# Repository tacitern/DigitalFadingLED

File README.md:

# DigitalFadingLED
Microcontroller project which uses a usb virtual serial port to control the color of a RGB led, brightness and fade rate.

## Serial Commands

The FadingLED device waits for specific serial commands. The following table lists the specifc commands:

|Serial Command|Command Message|
| :---- | :---- |
| [Get Colors](#get-colors) | `"COLOR?\r\n"` |
| [Set Colors](#set-colors) | `"COLOR <Red>,<Green>,<Blue>\r\n"` |
| [Get Luminance](#get-luminance) | `"LUM?\r\n"` |
| [Set Luminance](#set-luminance) | `"LUM <Luminance>\r\n"` |
| [Get Rate](#get-rate) | `"RATE?\r\n"` |
| [Set Rate](#set-rate) | `"RATE <Rate>\r\n"` |
| [Get Save Data](#get-save-data) | `"SAVE?\r\n"` |
| [Set Save Date](#set-save-data) | `"SAVE\r\n"` |
| [Get ID](#get-id) | `"ID?\r\n"` |
| [Set ID](#set-id) | `"ID <ID number>\r\n"` |

### **Get Colors**

Returns current color settings as unsigned integer values from 0 to 255

*Serial Command:* `"COLOR?\r\n"`

*Return String:* `"Red <0 to 255>; Green <0 to 255>; Blue <0 to 255>;\n\r"`

---

### **Set Colors**

Sets the current color setting using provided unsigned interger values for 0 to 255

*Serial Command:* `"COLOR <Red>,<Green>,<Blue>\n\r"`

---

### **Get Luminance**

Returns the current brightness/luminance setting as an unsigned integer from 0 to 1000

*Serial Command:* `"LUM?\n\r"`

*Return String:* `<Luminance Value>\n\r`

---

### **Set Luminance**

Sets the current brightness/luminance setting using a provided unsigned interger from 0 to 1000, 0 to 100.0 percent.

*Serial Command:* `"LUM <Luminance>\r\n"`

---

### **Get Rate**

Returns the current rate setting as an unsigned integer from 0 to 255.

*Serial Command:* `"RATE?\n\r"`

*Return String:* `<Rate Value>\n\r`

---

### **Set Rate**

Sets the current brightness/luminance setting using a provided unsigned interger from 0 to 1000, 0 to 100.0 percent.

*Serial Command:* `"LUM <Luminance>\r\n"`

---

### **Get Save Data**

Returns the current settings saved in the on board EEPROM.

*Serial Command:* `"SAVE?\r\n"`

*Return String:* `"ID: <ID Setting>\nRED: <Red Value>\nGREEN: <Green Value>\nBLUE: <Blue Value>\nLUM: <Luminance Value>\nRATE: <Rate Value>\n\r"`

---

### **Set Save Data**

Saves the current settings in the on board EEPROM. The settings saved include:

* ID Value
* Red Value
* Green Value
* Blue Value
* Luminance Value
* Rate Value

*Serial Command:* `"SAVE\r\n"`

---

### **Get ID**

Returns the current ID number setting saved in the EEPROM.

*Serial Command:* `"ID?\n\r"`

*Return String:* `<ID Number>\n\r`

---

### **Set ID**

Sets the provided unsigned integer from 0 to 255 as an ID number to be saved in the EEPROM. 

*Serial Command:* `"ID <ID Number>\n\r"`

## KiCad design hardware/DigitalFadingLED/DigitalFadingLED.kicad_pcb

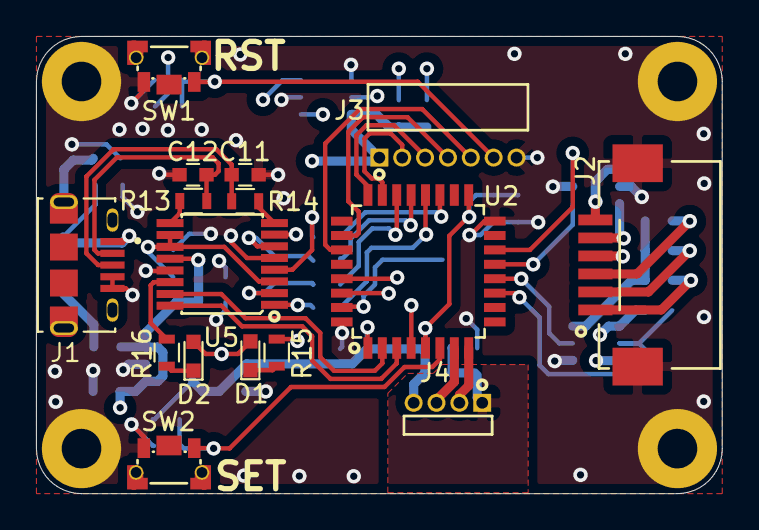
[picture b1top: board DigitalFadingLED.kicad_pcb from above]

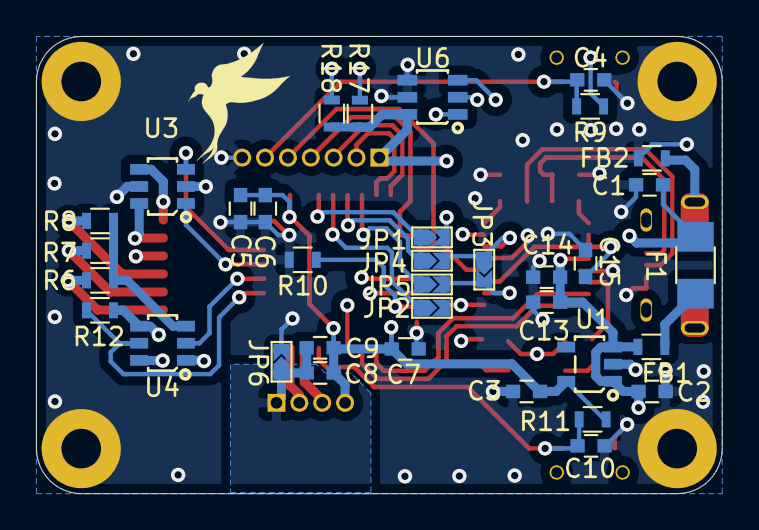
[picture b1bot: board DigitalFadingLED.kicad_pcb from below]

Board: 4 copper layers, 38.1 x 25.4 mm, 51 parts (35 on the bottom side), 47 nets.

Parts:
C1, C4, C6, C7, C8, C10, C13, C15: 0.1u; C_0603
C2, C3, C9: 1u; C_0603
C5: 10u; C_0603
C11, C12: 47p; C_0603
C14: 4.7u; C_0603
D1, D2: LED; LED_0603
F1: Polyfuse_Small; Fuse_SMD1206_Wave
FB1, FB2: Ferrite_Bead_Small; R_0603
J1: USB_B_Micro; AMPHENOL_10118194-0001LF
J2: molex_FFC_0522070633
J3: Conn_01x07; TMS-107-02-G-S-RA
J4: Conn_01x04; GRPB041VWCN-RC
JP1, JP2, JP3, JP4, JP5, JP6: jump
R6, R8: 200; R_0603
R7: 232; R_0603
R9, R10, R11, R12: 10k; R_0603
R13, R14: 27; R_0603
R15, R16: 270; R_0603
R17, R18: 2k; R_0603
SW1, SW2: SW_Push; TL6340AF160Q
U1: BU33SD5WG-TR; BU33SD5WG
U2: STM32L071KZTx; STM32L071KZT6
U3: QS6K21; QS6K21TR
U4: QS6M4; QS6K21TR
U5: FT230XS-U; FT230XS
U6: 34AA02

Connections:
+3.3VP: C15.1, D1.2, D2.2, U5.3, U5.10, U5.11
+3V3: C3.1, C5.1, C6.1, C7.1, C8.1, C9.1, J3.1, J4.4, R9.1, R11.1, R17.1, R18.1, U1.5, U2.1, U2.5, U2.17, U6.6
/EEPROM/SCL: R18.2, U2.29, U6.1
/EEPROM/SDA: R17.2, U2.30, U6.3
/LED Driver/LED_BLUE: J2.6, U3.4
/LED Driver/LED_GREEN: J2.5, U3.6
/LED Driver/LED_RED: J2.4, U4.6
/LED Driver/OUT_LUM: R6.2, R7.2, R8.2, U4.3
/LED Driver/TIM_BLUE: U2.14, U3.3
/LED Driver/TIM_GREEN: U2.13, U3.1
/LED Driver/TIM_LUM: R12.2, U2.11, U4.5
/LED Driver/TIM_RED: U2.12, U4.2
/MCU/CBUS0: U2.2, U5.15
/MCU/CBUS3: U2.3, U5.16
/MCU/NRST: C4.1, J3.6, R9.2, SW1.2, U2.4
/MCU/SWCLK: J3.3, U2.24
/MCU/SWDIO: J3.2, U2.23
/MCU/USART1_CTS: JP5.1, U2.22
/MCU/USART1_RTS: JP4.1, U2.21
/MCU/USART1_RX: JP2.1, U2.20
/MCU/USART1_TX: JP1.1, U2.19
/MCU/VCP_RX: J3.5, U2.27
/MCU/VCP_TX: J3.4, U2.26
/USB to Serial/CTS: JP3.1, JP4.2, U5.6
/USB to Serial/RTS: JP3.2, JP5.2, U5.2
/USB to Serial/RXD: JP1.2, U5.4
/USB to Serial/TXD: JP2.2, U5.1
/USB to Serial/USBDM: C12.1, J1.2, R13.2
/USB to Serial/USBDP: C11.1, J1.3, R14.2
GND: C1.2, C2.2, C3.2, C4.2, C5.2, C6.2, C7.2, C10.2, C11.2, C12.2, C13.2, C14.2, C15.2, FB2.1, J1.4, J1.5, J2.S, J3.7, JP6.2, R10.2, SW1.1, SW2.2, U1.2, U2.16, U2.32, U3.2, U3.5, U4.1, U5.5, U5.13, U6.2, U6.4, U6.5
GNDA: C8.2, C9.2, J4.1, JP6.1
unnamed: C1.1, F1.2, J1.1
unnamed: C10.1, R11.2, SW2.1, U2.6
unnamed: D1.1, R15.1
unnamed: D2.1, R16.1
unnamed: F1.1, FB1.2
unnamed: J2.1, R6.1
unnamed: J2.2, R7.1
unnamed: J2.3, R8.1
unnamed: J4.2, U2.8
unnamed: J4.3, U2.7
unnamed: R10.1, U2.31
unnamed: R13.1, U5.9
unnamed: R14.1, U5.8
unnamed: R15.2, U5.7
unnamed: R16.2, U5.14
VCC: C2.1, C13.1, C14.1, FB1.1, R12.1, U1.1, U1.3, U4.4, U5.12

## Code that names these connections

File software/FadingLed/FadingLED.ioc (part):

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Mcu.Name=STM32L071K(B-Z)Tx
Mcu.Package=LQFP32
Mcu.UserName=STM32L071KZTx
PA0.GPIOParameters=GPIO_Label
PA0.GPIO_Label=USER_BTN
PA0.Signal=GPIO_Input
PA1.Mode=IN1
PA1.Signal=ADC_IN1
PA10.Mode=Asynchronous
PA10.Signal=USART1_RX
PA11.Signal=USART1_CTS
PA12.Signal=USART1_RTS
PA13.Mode=Serial_Wire
PA13.Signal=SYS_SWDIO
PA14.Mode=Serial_Wire
PA14.Signal=SYS_SWCLK
PA2.Mode=IN2
PA2.Signal=ADC_IN2
PA5.GPIOParameters=GPIO_ModeDefaultPP,GPIO_Label
PA5.GPIO_Label=TIM_LUM
PA5.GPIO_ModeDefaultPP=GPIO_MODE_AF_OD
PA5.Signal=S_TIM2_CH1
PA6.GPIOParameters=GPIO_Label
PA6.GPIO_Label=TIM_RED
PA6.Signal=S_TIM3_CH1
PA7.GPIOParameters=GPIO_Label
PA7.GPIO_Label=TIM_GREEN
PA7.Signal=S_TIM3_CH2
PA9.Mode=Asynchronous
PA9.Signal=USART1_TX
PB0.GPIOParameters=GPIO_Label
PB0.GPIO_Label=TIM_BLUE
PB0.Signal=S_TIM3_CH3
PB3.Mode=Asynchronous
PB3.Signal=USART5_TX
PB4.Mode=Asynchronous
PB4.Signal=USART5_RX
PB6.GPIOParameters=GPIO_Pu
PB6.GPIO_Pu=GPIO_PULLUP
PB6.Mode=I2C
PB6.Signal=I2C1_SCL
PB7.GPIOParameters=GPIO_Pu
PB7.GPIO_Pu=GPIO_PULLUP
PB7.Mode=I2C
PB7.Signal=I2C1_SDA
PC14-OSC32_IN.GPIOParameters=GPIO_Label
PC14-OSC32_IN.GPIO_Label=CBUS0_TXDEN
PC14-OSC32_IN.Signal=GPIO_Input
PC15-OSC32_OUT.GPIOParameters=GPIO_Label
PC15-OSC32_OUT.GPIO_Label=CBUS3_\#SLEEP
PC15-OSC32_OUT.Signal=GPIO_Input
RCC.SYSCLKFreq_VALUE=32000000
RCC.SYSCLKSource=RCC_SYSCLKSOURCE_PLLCLK
board=custom

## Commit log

2021-08-27 Code is still in work, this is an initial functioning commit
2021-08-28 Added EEPROM ID Command
2021-09-01 Added 'SAVE?' serial shell command
    Added the command 'SAVE?'. This command list the current contents of the
    EEPROM.
2021-09-01 Added 'SAVE' command to Serial Shell
    'SAVE' command writes the current color, luminence and rate settings to
    thier respective EEPROM memory locations
2021-09-01 Added 'ID' command to the serial shell
    'ID' followed by an 8bit number sent through serial communication with
    the device allows the user to modify the device ID
2021-09-08 Added EEPROM Status Logging
2021-09-09 Added software folder
    Moved code into software folder
2021-09-09 Added underscore to stm32f4discovery dev code folder
2021-09-09 Initial hardware commit
2021-11-26 Added final V1 pcbs
    Added various component files
    Added kicad files and gerbers for LED board, Digital Board, and
    proggramming adpter boards
2021-12-28 Initial software for L0 micro
2021-12-28 Added pdfs for board schematics
2021-12-30 Fixed Luminance Inversion
    Because P channel fet which controls luminance is active low larger
    luminance values were causing decreases in brightness. This is now
    accounted for and tested.
    TODO:
    -Fix Luminance and Color Timer apparent phase issues:
    --When luminence is used there is a flicker, this only happens when the
2022-02-13 Large software update
    Updated string related function to use standard libraries
    Added Doxygen documentation to functions
    Updated luminance timing to 9.495kHz to deal with color flicker issues
    TODO
    Investigate potential beating with luminance and color PWM, suggested
    fix for color flicker; still do not fully understand fix
2022-04-11 Added Documentation
2022-04-11 Update README.md
    fixed centering
2022-04-11 Update README.md
    updated ID number information
2022-04-12 First cut command line util
2022-04-12 added installer
